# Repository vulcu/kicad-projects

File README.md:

# kicad-projects
KiCad Projects

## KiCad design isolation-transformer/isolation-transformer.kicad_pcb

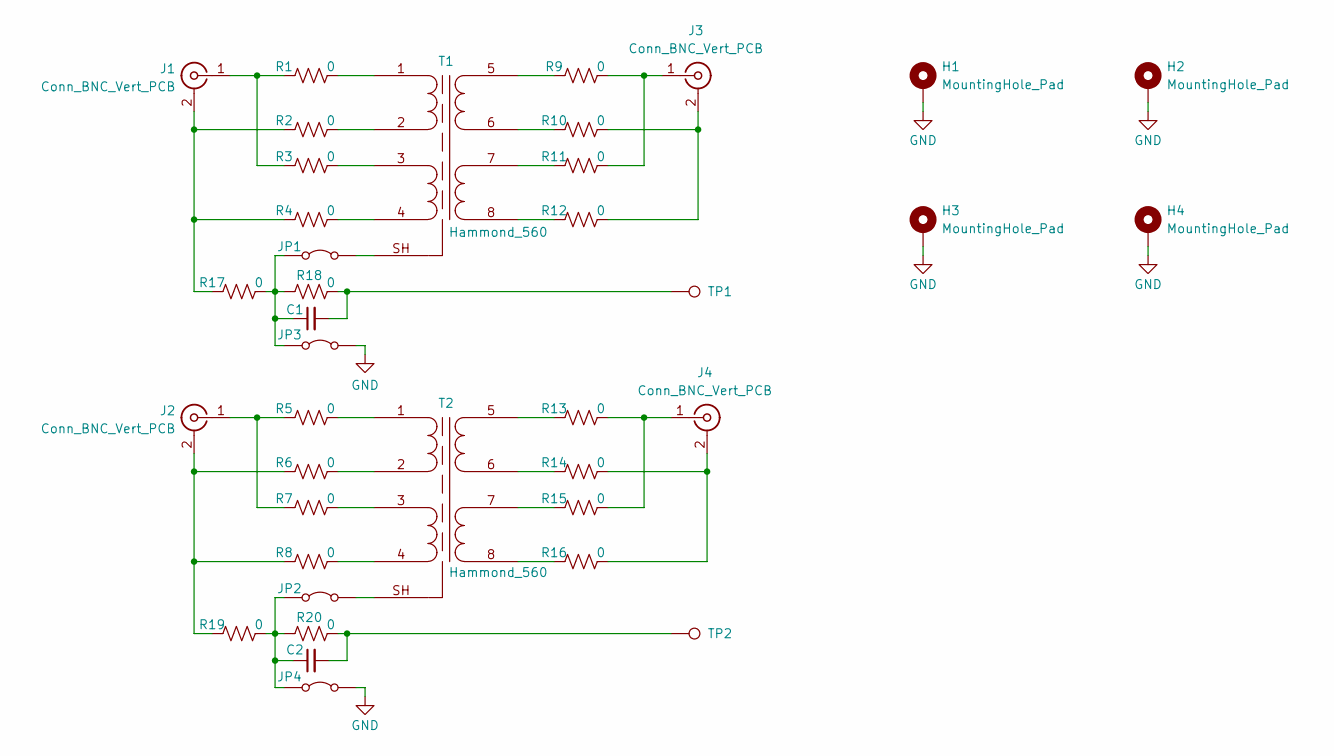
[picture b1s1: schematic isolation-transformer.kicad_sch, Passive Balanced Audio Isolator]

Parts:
C1, C2: C_Small; C_0603_1608Metric_Pad1.08x0.95mm_HandSolder
H1, H2, H3, H4: MountingHole_Pad; MountingHole_3.2mm_M3_Pad
J1, J2, J3, J4: Conn_BNC_Vert_PCB; AMPHENOL_112405-12
JP1, JP2, JP3, JP4: Jumper_2_Bridged; TestPoint_2Pads_Pitch2.54mm_Drill0.8mm
R1, R2, R3, R4, R5, R6, R7, R8, R9, R10, R11, R12, R13, R14, R15, R16, R17, R18, R19, R20: 0; R_0603_1608Metric_Pad0.98x0.95mm_HandSolder
T1, T2: Hammond_560; XFMR_3302W64P508L4166H216Q9B
TP1, TP2: TestPoint; PinHeader_1x01_P1.00mm_Vertical

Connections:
GND: H1.1, H2.1, H3.1, H4.1, JP3.2 (B), JP4.2 (B)
unnamed: C1.2, R18.2, TP1.1
unnamed: C2.2, R20.2, TP2.1
unnamed: J1.2 (Ext), R2.1, R4.1, R17.1
unnamed: J1.1 (In), R1.1, R3.1
unnamed: J2.2 (Ext), R6.1, R8.1, R19.1
unnamed: J2.1 (In), R5.1, R7.1
unnamed: J3.2 (Ext), R10.2, R12.2
unnamed: J3.1 (In), R9.2, R11.2
unnamed: J4.2 (Ext), R14.2, R16.2
unnamed: J4.1 (In), R13.2, R15.2
unnamed: C1.1, JP1.1 (A), JP3.1 (A), R17.2, R18.1
unnamed: JP1.2 (B), T1.SH (IN2B)
unnamed: C2.1, JP2.1 (A), JP4.1 (A), R19.2, R20.1
unnamed: JP2.2 (B), T2.SH (IN2B)
unnamed: R4.2, T1.4 (IN2B)
unnamed: R8.2, T2.4 (IN2B)
unnamed: R1.2, T1.1 (IN1A)
unnamed: R2.2, T1.2 (IN1B)
unnamed: R3.2, T1.3 (IN2A)
unnamed: R9.1, T1.5 (OUT1A)
unnamed: R10.1, T1.6 (OUT1B)
unnamed: R11.1, T1.7 (OUT2A)
unnamed: R12.1, T1.8 (OUT2B)
unnamed: R5.2, T2.1 (IN1A)
unnamed: R6.2, T2.2 (IN1B)
unnamed: R7.2, T2.3 (IN2A)
unnamed: R13.1, T2.5 (OUT1A)
unnamed: R14.1, T2.6 (OUT1B)
unnamed: R15.1, T2.7 (OUT2A)
unnamed: R16.1, T2.8 (OUT2B)

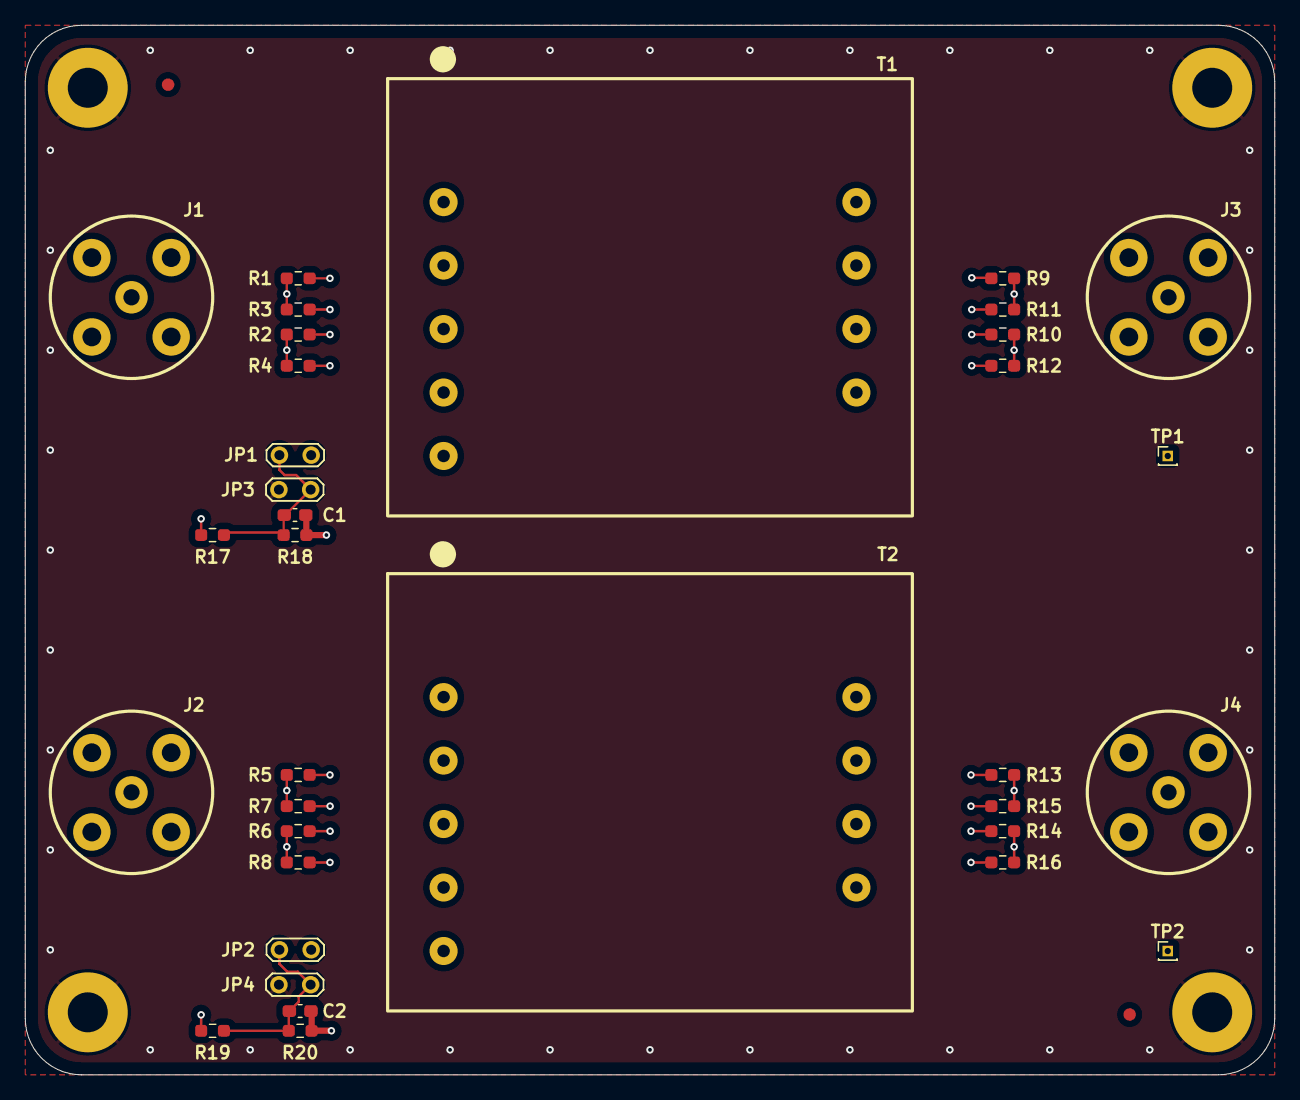
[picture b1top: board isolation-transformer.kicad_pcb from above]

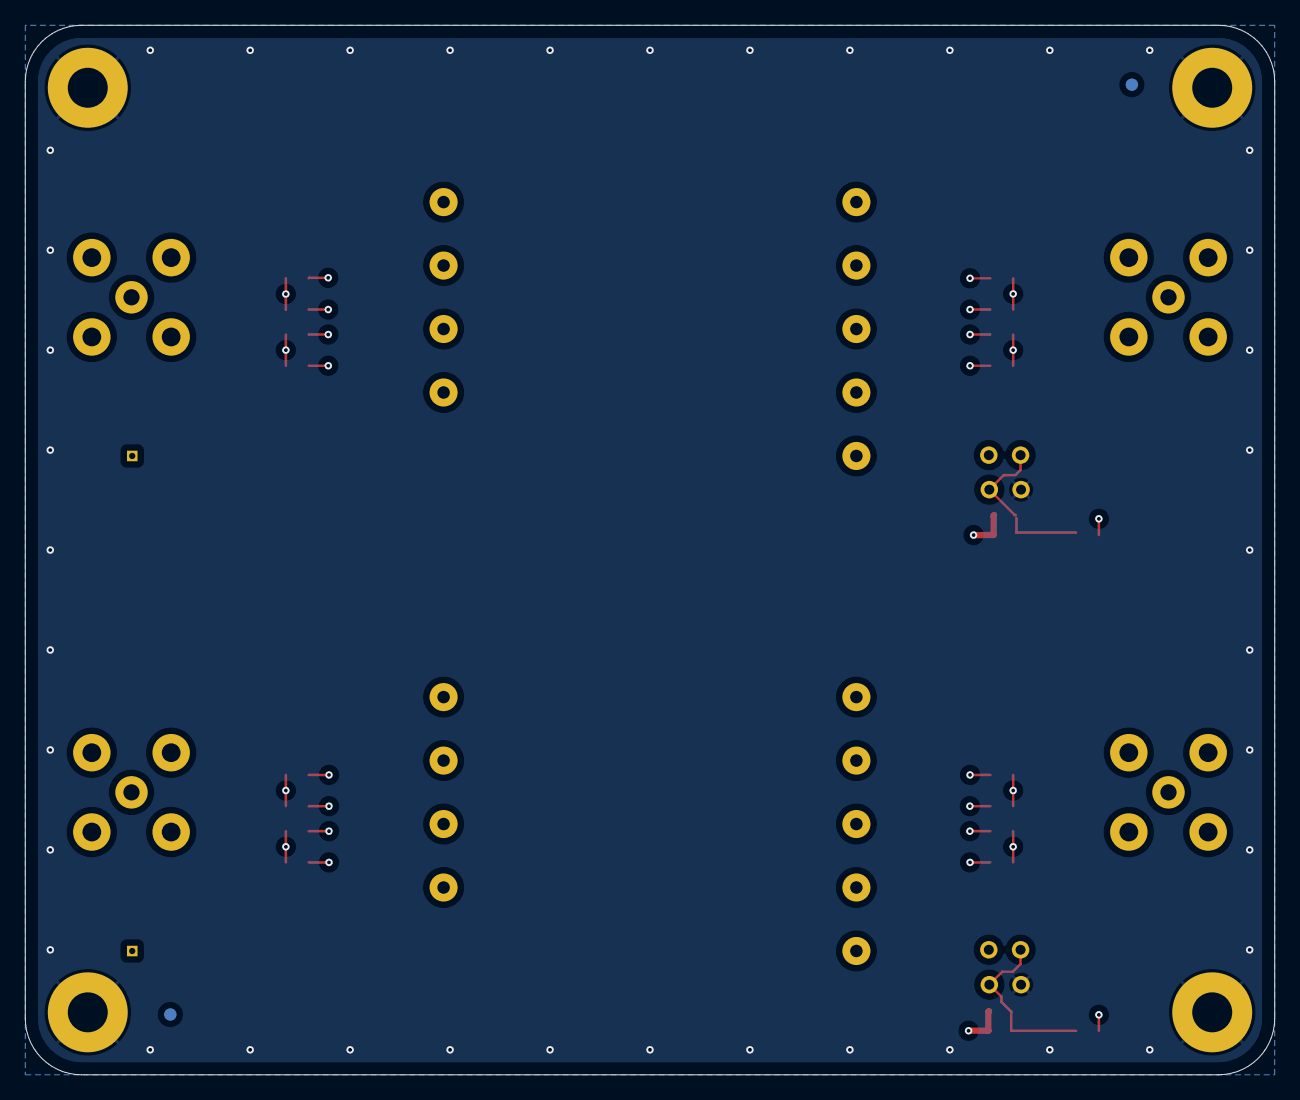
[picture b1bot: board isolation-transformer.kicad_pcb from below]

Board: 4 copper layers, 100.0 x 84.0 mm, 42 parts (2 on the bottom side), 31 nets.

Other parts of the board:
FD1, FD2, FD3, FD4: Fiducial_1mm_Mask2mm

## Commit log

2024-04-23 feat: init commit of isolation-xfmr
2024-04-24 fix: add shield pin connect options
2024-05-06 feat: add 3D models and GND jmpr
2024-05-09 feat: input signal routing
2024-05-10 feat: secondary side routing and GND zones
2024-05-23 chore: update gitignore
2024-05-23 feat: routing of iso-xfmr complete
2024-06-04 chore: align mtg holes and conns, add perimiter GND vias
2024-09-05 feat: add bypass caps to GND connection
2025-02-22 refactor: begin reposition of 0-Ohm links for tighter signal coupling
2025-04-23 fix (PCB): zero-ohm resistor alignment mismatch between in/out
2025-08-06 fix (PCB): move L1 traces to L3, update TP footprint
2026-01-05 docs: add `CONTRIBUTING.md` guide
2026-01-05 chore (captouch-keyboard): create new project subdirectory and add initial docs and mcad files
2026-01-06 Added updated mockups
    PNG & SVG
2026-01-06 Added affinity file
2026-01-13 feat (captouch-kbd): create KiCad project files

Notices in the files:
isolation-transformer/isolation-transformer.kicad_pcb:
©2024 Winry Litwa-Vulcu
